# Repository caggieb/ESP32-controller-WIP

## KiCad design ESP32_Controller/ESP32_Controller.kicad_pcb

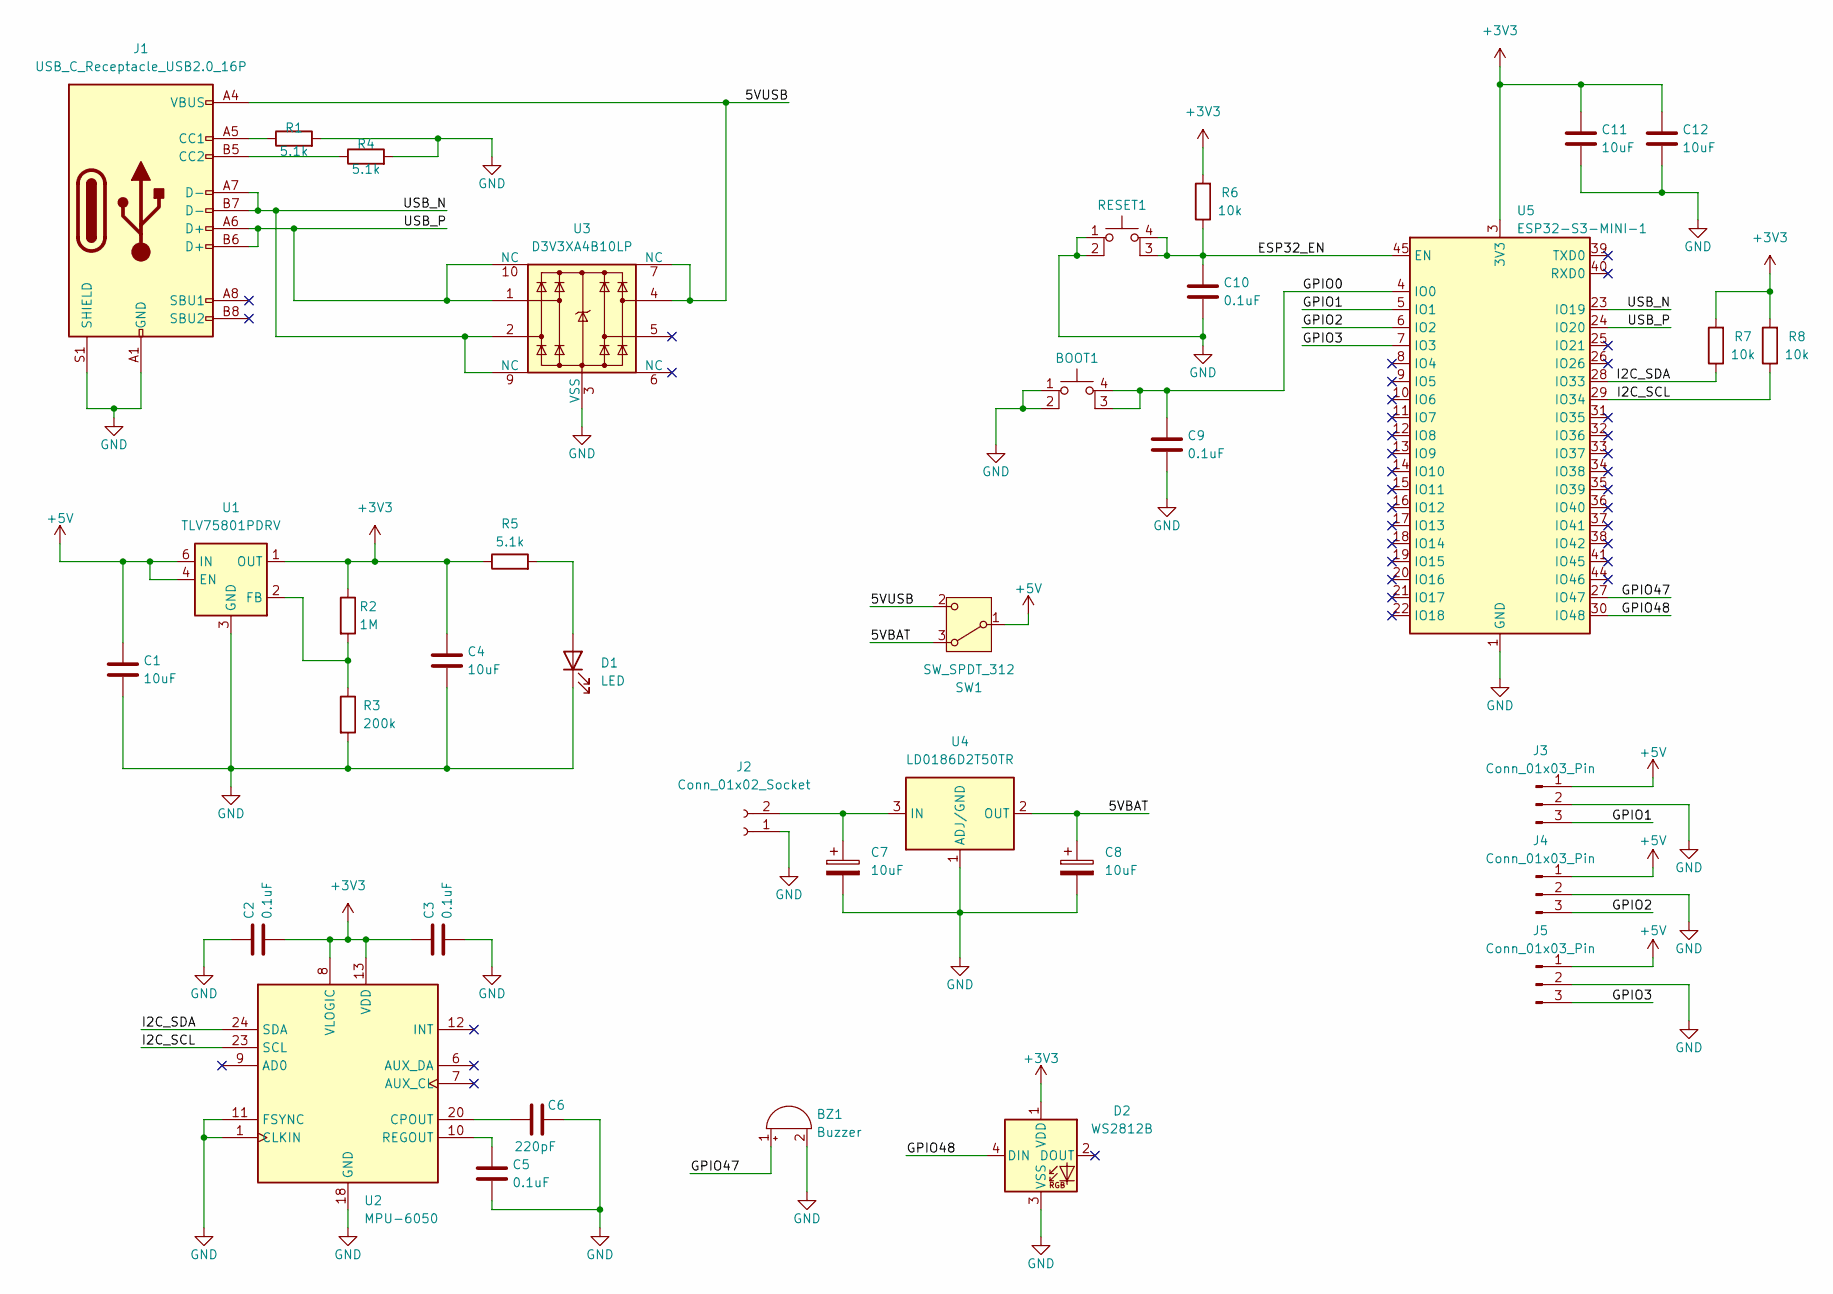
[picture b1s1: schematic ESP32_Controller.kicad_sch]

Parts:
BOOT1: SW_MEC_5E; SW_SPST_PTS810
BZ1: Buzzer; Buzzer_Murata_PKMCS0909E
C1, C4, C11, C12: 10uF; C_0603_1608Metric
C2, C3, C5, C9, C10: 0.1uF; C_0603_1608Metric
C6: 220pF; C_0603_1608Metric
C7, C8: 10uF; C_0805_2012Metric
D1: LED; LED_0603_1608Metric
D2: WS2812B; LED_WS2812B_PLCC4_5.0x5.0mm_P3.2mm
J1: USB_C_Receptacle_USB2.0_16P; USB_C_Receptacle_GCT_USB4105-xx-A_16P_TopMnt_Horizontal
J2: Conn_01x02_Socket; AMASS_XT60-F_1x02_P7.20mm_Vertical
J3, J4, J5: Conn_01x03_Pin; PinHeader_1x03_P2.54mm_Vertical
R1, R4, R5: 5.1k; R_0603_1608Metric
R2: 1M; R_0603_1608Metric
R3: 200k; R_0603_1608Metric
R6, R7, R8: 10k; R_0603_1608Metric
RESET1: SW_MEC_5E; SW_SPST_PTS810
SW1: SW_SPDT_312; SW_Slide_SPDT_Straight_CK_OS102011MS2Q
U1: TLV75801PDRV; WSON-6-1EP_2x2mm_P0.65mm_EP1x1.6mm
U2: MPU-6050; InvenSense_QFN-24_4x4mm_P0.5mm
U3: D3V3XA4B10LP; Diodes_UDFN-10_1.0x2.5mm_P0.5mm
U4: LD0186D2T50TR; TO-263-2
U5: ESP32-S3-MINI-1; XCVR_ESP32-S3-MINI-1-N8

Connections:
+3V3: C2.2, C3.1, C4.1, C11.1, C12.1, D2.1 (VDD), R2.1, R5.1, R6.2, R7.2, R8.2, U1.1 (OUT), U2.8 (VLOGIC), U2.13 (VDD), U5.3 (3V3)
+5V: C1.1, J3.1, J4.1, J5.1, SW1.1 (B), U1.4 (EN), U1.6 (IN)
/5VBAT: C8.1, SW1.3 (A), U4.2 (OUT)
/5VUSB: J1.A4 (VBUS), J1.A9 (VBUS), J1.B4 (VBUS), J1.B9 (VBUS), SW1.2 (C), U3.4, U3.7 (NC)
/ESP32_EN: C10.1, R6.1, RESET1.3 (K), RESET1.4 (A), U5.45 (EN)
/GPIO0: BOOT1.3 (K), BOOT1.4 (A), C9.1, U5.4 (IO0)
/GPIO1: J3.3, U5.5 (IO1)
/GPIO2: J4.3, U5.6 (IO2)
/GPIO3: J5.3, U5.7 (IO3)
/GPIO47: BZ1.1 (+), U5.27 (IO47)
/GPIO48: D2.4 (DIN), U5.30 (IO48)
/I2C_SCL: R8.1, U2.23 (SCL), U5.29 (IO34)
/I2C_SDA: R7.1, U2.24 (SDA), U5.28 (IO33)
/USB_N: J1.A7 (D-), J1.B7 (D-), U3.2, U3.9 (NC), U5.23 (IO19)
/USB_P: J1.A6 (D+), J1.B6 (D+), U3.1, U3.10 (NC), U5.24 (IO20)
GND: BOOT1.1, BOOT1.2, BZ1.2 (-), C1.2, C2.1, C3.2, C4.2, C5.2, C6.2, C7.2, C8.2, C9.2, C10.2, C11.2, C12.2, D1.1 (K), D2.3 (VSS), J1.A1 (GND), J1.A12 (GND), J1.B1 (GND), J1.B12 (GND), J1.S1 (SHIELD), J2.1, J3.2, J4.2, J5.2, R1.2, R3.2, R4.2, RESET1.1, RESET1.2, U1.3 (GND), U1.7 (GND), U2.1 (CLKIN), U2.11 (FSYNC), U2.18 (GND), U3.3 (VSS), U3.8 (VSS), U4.1 (ADJ/GND), U5.1 (GND), U5.2 (GND), U5.42 (GND), U5.43 (GND), U5.46 (GND), U5.47 (GND), U5.48 (GND), U5.49 (GND), U5.50 (GND), U5.51 (GND), U5.52 (GND), U5.53 (GND), U5.54 (GND), U5.55 (GND), U5.56 (GND), U5.57 (GND), U5.58 (GND), U5.59 (GND), U5.60 (GND), U5.61 (GND), U5.62 (GND), U5.63 (GND), U5.64 (GND), U5.65 (GND)
unnamed: D1.2 (A), R5.2
unnamed: J1.A5 (CC1), R1.1
unnamed: J1.B5 (CC2), R4.1
unnamed: C7.1, J2.2, U4.3 (IN)
unnamed: R2.2, R3.1, U1.2 (FB)
unnamed: C6.1, U2.20 (CPOUT)
unnamed: C5.1, U2.10 (REGOUT)

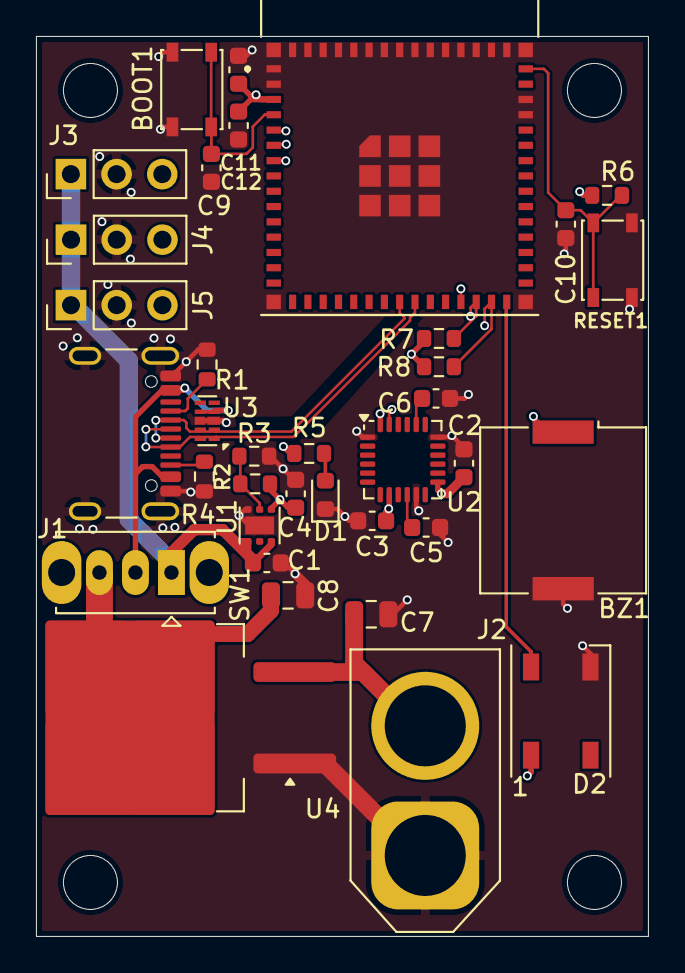
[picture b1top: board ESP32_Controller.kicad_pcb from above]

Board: 4 copper layers, 34.0 x 50.0 mm, 36 parts (0 on the bottom side), 23 nets.

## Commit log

2024-10-08 added current version of kicad files
2024-10-08 restructure
2024-10-08 deleted, old gerber files
    Old gerber files were used to estimate the manufacturing cost. However, the design is not finalized, thus they are abundant.
